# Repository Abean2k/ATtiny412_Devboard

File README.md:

# ATtiny412_Devboard

Uses an ATtiny 412 or the 212 as the MCU for a very cheap and small dev-board. Developed alongside the USB serial to UDPI Programmer.

## SPECS:
The devboard works with both an ATtiny 412 and an ATtiny 212 in the SOT 8 form-factor. These MCU's have a total of 8 pins. Here are the pinouts for each pin (will be replaced with devboard pinout later):

### ATtiny412 (Recomended Option):
#### Flash: 4 KB
#### SRAM: 256 B
#### EEPROM: 128 B
### ATtiny212: 
#### Flash: 2 KB
#### SRAM: 128 B
#### EEPROM: 64 B

## HOW TO USE:
1. Install or Open Arduino
2. Go to File < Preferences < Additional Boards Manager URLs and paste in "http://drazzy.com/package_drazzy.com_index.json"
3. Go to Tools < Board: and select "ATtiny412/402/212/202"
4. Go to Tools < Clock: and select "20 MHz Internal"
6. Search up and install CH340N Drivers
7. Connect Programmer 3 pins to Devboard 3 pins

8. Flash LED Blink Code
9. It Should Work:)

## PCB:
I made two layer PCBs for each of the two boards. I added ground pours and thicker power traces for hgiher relizablity and more compact size. The devboard user breakouts are breadboard sized and spaced. 
All components are designed to be hand solderable. Note: UPDI pin is not broken out on devboard (SO DNC) to the other user pins as it needs to be kept clear for programming. 

### Devboard Schematic:

### Programmer Schematic:

### Devboard PCB:

### Programmer PCB:

## BOM:
### SerialUPDI Programmer Board
| Component Reference | Description | Package Type | Purpose |
| :--- | :--- | :--- | :--- |
| **U1** | CH340N USB-to-Serial Bridge | SOIC-8 (SOP-8) | Translates computer USB commands into serial data |
| **J2** | USB 2.0 Type-A Male Plug | SMT Edge Mount | Plugs directly into the computer's USB port |
| **R1** | 4.7 kΩ Resistor | SMD (0805) | Junction resistor connecting TXD and RXD for single-wire UPDI |
| **R2** | 1 kΩ Resistor | SMD (0805) | Current-limiting resistor for the Power LED indicator |
| **C1** | 100 nF Ceramic Capacitor | SMD (0805) | Decoupling capacitor for internal V3 regulator (Pin 1) |
| **C2** | 100 nF Ceramic Capacitor | SMD (0805) | Decoupling capacitor for VCC supply line (Pin 7) |
| **D1** | Indicator LED | SMD (0805) | Power-on safety indicator |

### ATtiny412 Student Devboard
| Component Reference | Description | Package Type | Purpose |
| :--- | :--- | :--- | :--- |
| **U1** | ATtiny412 Microcontroller | SOIC-8 (SOP-8) | Main programmable brain (4KB Flash, 256B SRAM) |
| **J1** | 6-Pin USB-C Receptacle | SMT (Single Row Pins) | Supplies power to the board from standard USB cables |
| **R1** | 10 kΩ Resistor | SMD (0805) | UPDI line pull-up|
| **R2** | 1 kΩ Resistor | SMD (0805) | Current-limiting resistor for the user indicator LED |
| **C1** | 100 nF Ceramic Capacitor | SMD (0805) | Main VCC supply line noise decoupling |
| **D1** | User LED | SMD (0805) | Built-in general indicator connected to pin **PA3** (Digital 4) |
| **U2** | AP2112K-3.3 | SOT-23-5 | High-speed 3.3V Linear Regulator for stable chip voltage |
| **Headers**| 2.54mm Breakaway Pins | Through-Hole | Breadboard formate pin breakout rails |

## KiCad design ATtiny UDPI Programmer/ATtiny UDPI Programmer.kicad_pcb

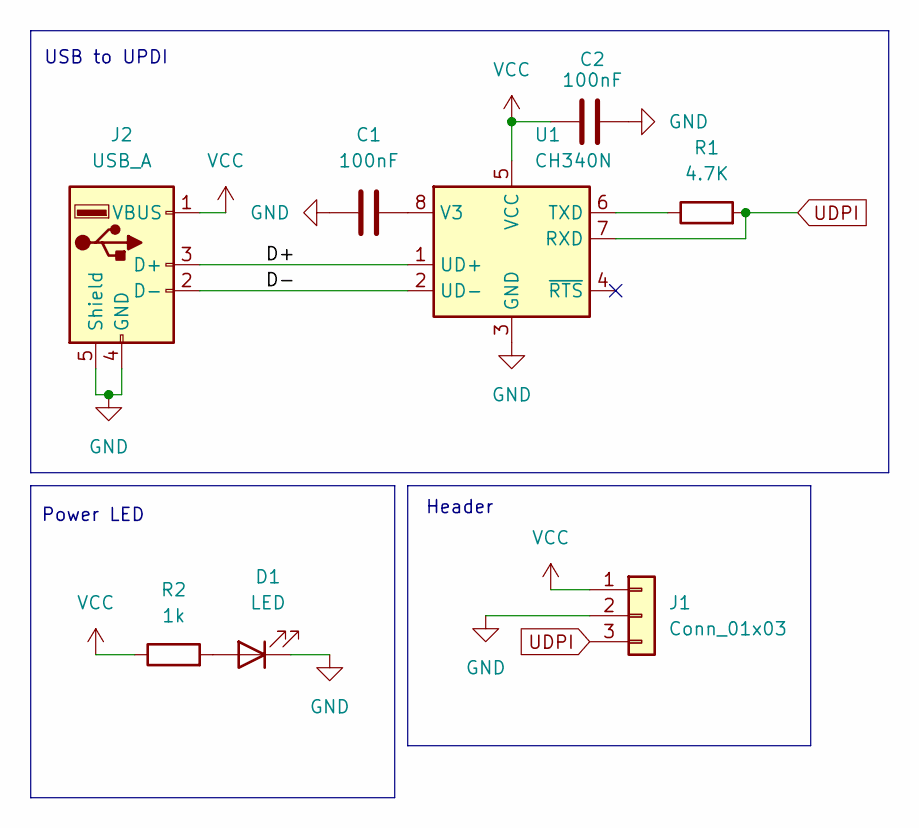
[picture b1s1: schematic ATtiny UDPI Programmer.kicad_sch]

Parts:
C1, C2: 100nF; C_0805_2012Metric_Pad1.18x1.45mm_HandSolder
D1: LED; LED_0805_2012Metric_Pad1.15x1.40mm_HandSolder
J1: Conn_01x03; PinSocket_1x03_P2.54mm_Vertical
J2: USB_A; USB_A_CNCTech_1001-011-01101_Horizontal
R1: 4.7K; R_0805_2012Metric_Pad1.20x1.40mm_HandSolder
R2: 1k; R_0805_2012Metric_Pad1.20x1.40mm_HandSolder
U1: CH340N; JEITA_SOIC-8_3.9x4.9mm_P1.27mm

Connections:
/D+: J2.3 (D+), U1.1 (UD+)
/D-: J2.2 (D-), U1.2 (UD-)
GND: C1.2, C2.2, D1.1 (K), J1.2, J2.4 (GND), J2.5 (Shield), U1.3 (GND)
unnamed: D1.2 (A), R2.2
unnamed: R1.1, U1.6 (TXD)
unnamed: C1.1, U1.8 (V3)
UDPI: J1.3, R1.2, U1.7 (RXD)
VCC: C2.1, J1.1, J2.1 (VBUS), R2.1, U1.5 (VCC)

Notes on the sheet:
Header
USB to UPDI
Power LED

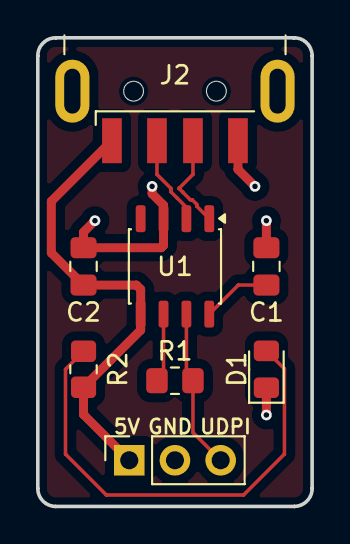
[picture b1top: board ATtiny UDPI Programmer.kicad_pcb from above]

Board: 2 copper layers, 15.2 x 26.0 mm, 8 parts (0 on the bottom side), 8 nets.

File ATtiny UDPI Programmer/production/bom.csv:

Designator,Footprint,Quantity,Value,LCSC Part #
"C1, C2",0805,2,100nF,
D1,0805,1,LED,
J1,PinSocket_1x03_P2.54mm_Vertical,1,Conn_01x03,
J2,USB_A_CNCTech_1001-011-01101_Horizontal,1,USB_A,
R1,0805,1,4.7K,
R2,0805,1,1k,
U1,JEITA_SOIC-8_3.9x4.9mm_P1.27mm,1,CH340N,

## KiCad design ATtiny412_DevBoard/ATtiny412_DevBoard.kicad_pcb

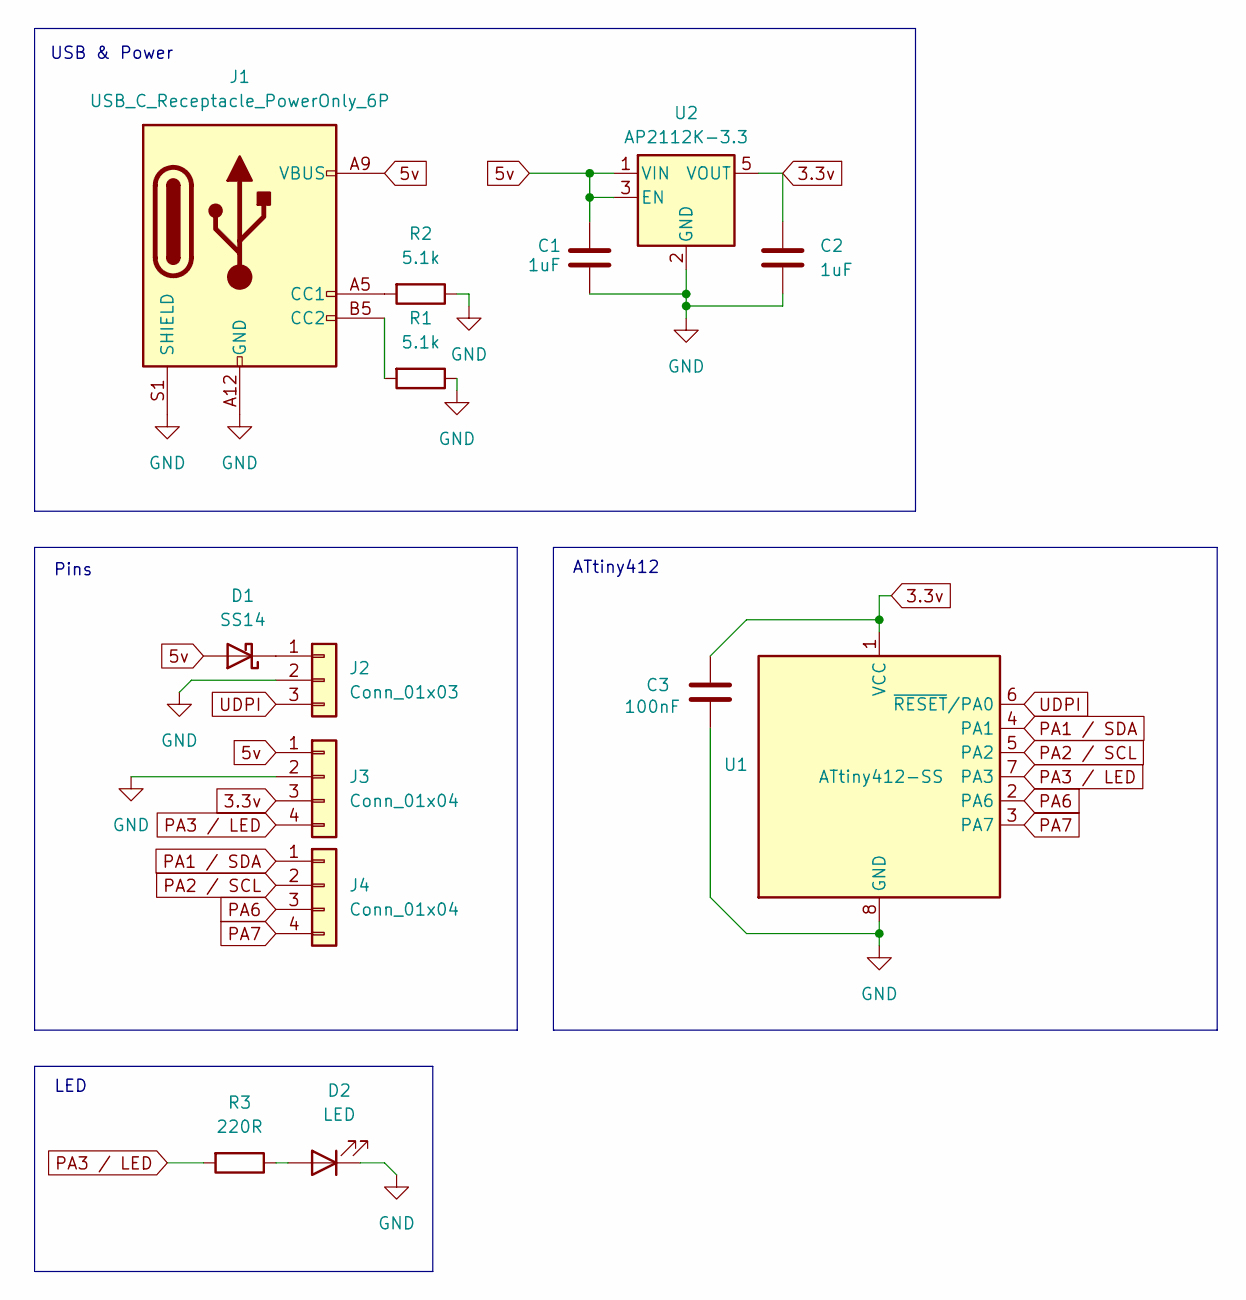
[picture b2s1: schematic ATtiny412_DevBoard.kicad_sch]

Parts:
C1, C2: 1uF; C_0805_2012Metric_Pad1.18x1.45mm_HandSolder
C3: 100nF; C_0805_2012Metric_Pad1.18x1.45mm_HandSolder
D1: SS14; D_SMA_Handsoldering
D2: LED; LED_0805_2012Metric_Pad1.15x1.40mm_HandSolder
J1: USB_C_Receptacle_PowerOnly_6P; USB_C_Receptacle_HRO_TYPE-C-31-M-17
J2: Conn_01x03; PinHeader_1x03_P2.54mm_Vertical
J3, J4: Conn_01x04; PinHeader_1x04_P2.54mm_Vertical
R1, R2: 5.1k; R_0805_2012Metric_Pad1.20x1.40mm_HandSolder
R3: 220R; R_1206_3216Metric_Pad1.30x1.75mm_HandSolder
U1: ATtiny412-SS; SOIC-8_3.9x4.9mm_P1.27mm
U2: AP2112K-3.3; SOT-23-5

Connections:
3.3v: C2.1, C3.1, J3.3, U1.1 (VCC), U2.5 (VOUT)
5v: C1.1, D1.2 (A), J1.A9 (VBUS), J1.B9 (VBUS), J3.1, U2.1 (VIN), U2.3 (EN)
GND: C1.2, C2.2, C3.2, D2.1 (K), J1.A12 (GND), J1.B12 (GND), J1.S1 (SHIELD), J2.2, J3.2, R1.1, R2.1, U1.8 (GND), U2.2 (GND)
unnamed: D1.1 (K), J2.1
unnamed: D2.2 (A), R3.1
unnamed: J1.A5 (CC1), R2.2
unnamed: J1.B5 (CC2), R1.2
PA1 / SDA: J4.1, U1.4 (PA1)
PA2 / SCL: J4.2, U1.5 (PA2)
PA3 / LED: J3.4, R3.2, U1.7 (PA3)
PA6: J4.3, U1.2 (PA6)
PA7: J4.4, U1.3 (PA7)
UDPI: J2.3, U1.6 (~RESET/PA0)

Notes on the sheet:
LED
USB & Power
ATtiny412
Pins

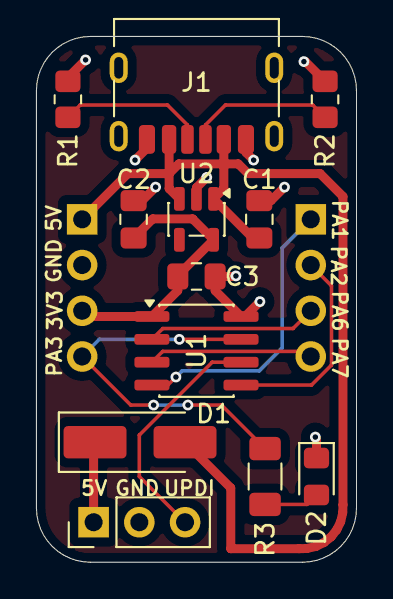
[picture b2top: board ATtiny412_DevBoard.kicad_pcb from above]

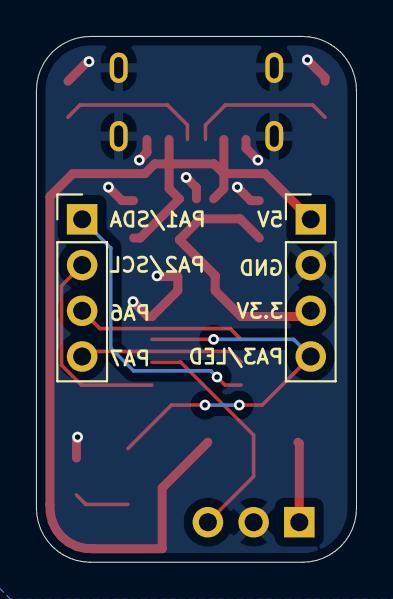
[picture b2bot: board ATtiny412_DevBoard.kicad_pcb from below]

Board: 2 copper layers, 17.8 x 29.2 mm, 14 parts (2 on the bottom side), 13 nets.

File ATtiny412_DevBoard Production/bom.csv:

Designator,Footprint,Quantity,Value,LCSC Part #
"C1, C2",0805,2,1uF,
C3,0805,1,100nF,
D1,D_SMA_Handsoldering,1,SS14,
D2,0805,1,LED,
J1,USB_C_Receptacle_HRO_TYPE-C-31-M-17,1,USB_C_Receptacle_PowerOnly_6P,
J2,PinHeader_1x03_P2.54mm_Vertical,1,Conn_01x03,
"J3, J4",PinHeader_1x04_P2.54mm_Vertical,2,Conn_01x04,
"R1, R2",0805,2,5.1k,
R3,1206,1,220R,
U1,SOIC-8_3.9x4.9mm_P1.27mm,1,ATtiny412-SS,
U2,SOT-23-5,1,AP2112K-3.3,

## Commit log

2026-06-06 All PCB and Kicad Files
2026-06-06 Added Test Code
2026-06-06 Update README with UPDI pin information
2026-06-06 Fix heading formatting for BOM section in README
2026-06-06 organized files
2026-06-06 Add BOM sections for Programmer PCB and ATtiny412 board
2026-06-06 Edited BOM
